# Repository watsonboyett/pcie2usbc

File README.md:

# miniPCIe to USB-C Adaptoid

A PCIe to USB-C adapter board -- plugs into a PCIe 1x card slot to breakout the data and clock lanes to a USB-C connector. 
Includes AC coupling caps and jumper resistors to aid in debugging/hacking.
Tested up to PCIe Gen 2 at 5.0 Gbps (though threre's plenty of room for improving the signal integrity).

[*] in 2nd step updating to PCIe 3.0 Standart

### Schematic

#### 
#### 
#### 

### PCB Bottom Side

#### 

### PCB Top Side

####

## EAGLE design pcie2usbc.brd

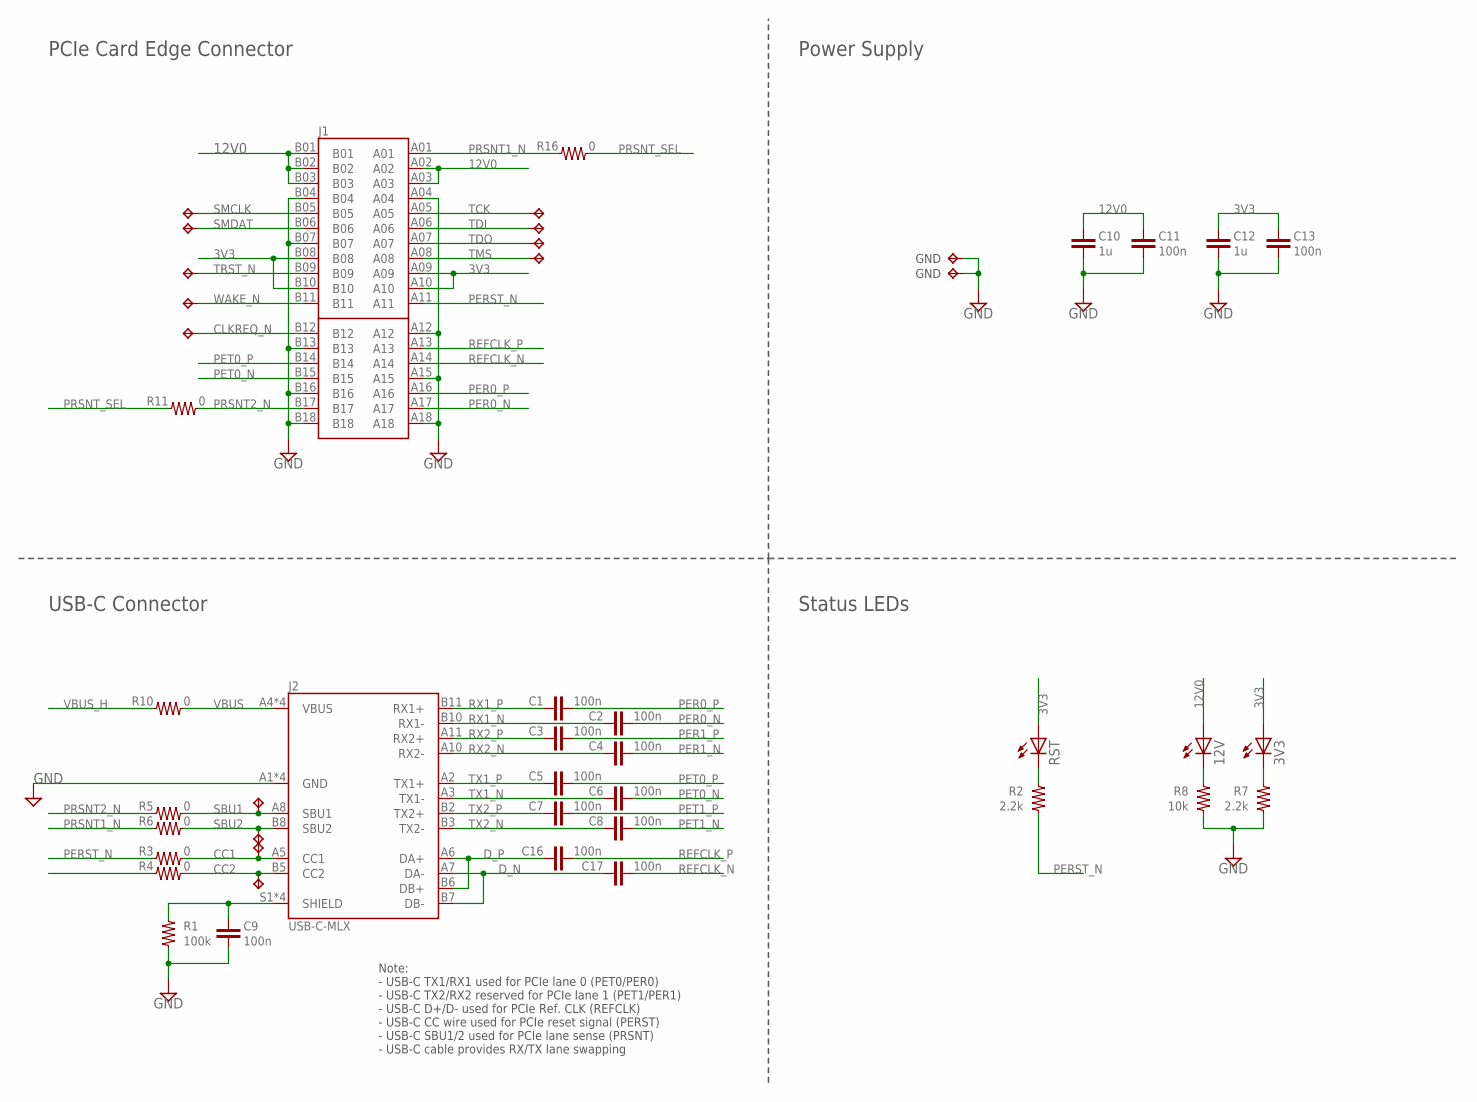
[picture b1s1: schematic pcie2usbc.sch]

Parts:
3V3, 12V: LEDSML0805; SML0805
C1, C2, C3, C4, C5, C6, C7, C8, C16, C17: 100n; C0402
C9, C11, C13: 100n; C0603K; MPN CC0603KRX7R8BB104
C10, C12: 1u; C0603K; MPN CC0603KRX7R8BB104
J1: PCIE-036-02-X-D-EMS2; SAMTEC_PCIE-036-02-X-D-EMS2
J2: USB-C-MLX; MOLEX_105450-0101
R1: 100k; R0603; MPN RC0603FR-07100KL
R2, R7: 2.2k; R0603
R3, R4, R5, R6, R10, R11, R16: 0; R0603
R8: 10k; R0603
RST: LEDSML0805; SML0805
TP1, TP2, TP3, TP4, TP5, TP6, TP7, TP8, TP9, TP11, TP12, TP16, TP21: TPB0,635; B0,635
TP10, TP13: TPTP38X20; TP38X20

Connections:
3V3: 3V3.A, C12.1, C13.1, J1.A09, J1.A10, J1.B08, J1.B10, RST.A
12V0: 12V.A, C10.1, C11.1, J1.A02, J1.A03, J1.B01, J1.B02, J1.B03
CC1: J2.A5 (CC1), R3.2, TP21.TP
CC2: J2.B5 (CC2), R4.1, TP16.TP
CLKREQ_N: J1.B12, TP9.TP
D_N: C17.1, J2.A7 (DA-), J2.B7 (DB-)
D_P: C16.1, J2.A6 (DA+), J2.B6 (DB+)
GND: C9.2, C10.2, C11.2, C12.2, C13.2, J1.A04, J1.A12, J1.A15, J1.A18, J1.B04, J1.B07, J1.B13, J1.B16, J1.B18, J2.A1 (GND), J2.A12 (GND), J2.B1 (GND), J2.B12 (GND), R1.1, R7.1, R8.1, TP10.TP, TP13.TP
unnamed: 12V.C, R8.2
unnamed: 3V3.C, R7.2
unnamed: R2.2, RST.C
PER0_N: C2.2, J1.A17
PER0_P: C1.2, J1.A16
PER1_N: C4.2
PER1_P: C3.2
PERST_N: J1.A11, R2.1, R3.1
PET0_N: C6.2, J1.B15
PET0_P: C5.2, J1.B14
PET1_N: C8.2
PET1_P: C7.2
PRSNT1_N: J1.A01, R6.1, R16.1
PRSNT2_N: J1.B17, R5.1, R11.2
PRSNT_SEL: R11.1, R16.2
REFCLK_N: C17.2, J1.A14
REFCLK_P: C16.2, J1.A13
RX1_N: C2.1, J2.B10 (RX1-)
RX1_P: C1.1, J2.B11 (RX1+)
RX2_N: C4.1, J2.A10 (RX2-)
RX2_P: C3.1, J2.A11 (RX2+)
SBU1: J2.A8 (SBU1), R5.2, TP11.TP
SBU2: J2.B8 (SBU2), R6.2, TP12.TP
SMCLK: J1.B05, TP5.TP
SMDAT: J1.B06, TP6.TP
TCK: J1.A05, TP1.TP
TDI: J1.A06, TP2.TP
TDO: J1.A07, TP3.TP
TMS: J1.A08, TP4.TP
TRST_N: J1.B09, TP7.TP
TX1_N: C6.1, J2.A3 (TX1-)
TX1_P: C5.1, J2.A2 (TX1+)
TX2_N: C8.1, J2.B3 (TX2-)
TX2_P: C7.1, J2.B2 (TX2+)
USB_SHLD1: C9.1, J2.S1 (SHIELD), J2.S2 (SHIELD), J2.S3 (SHIELD), J2.S4 (SHIELD), R1.2
VBUS: J2.A4 (VBUS), J2.A9 (VBUS), J2.B4 (VBUS), J2.B9 (VBUS), R10.2
VBUS_H: R10.1
WAKE_N: J1.B11, TP8.TP

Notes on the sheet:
PCIe Card Edge Connector
USB-C Connector
Power Supply
Note: - USB-C TX1/RX1 used for PCIe lane 0 (PET0/PER0) - USB-C TX2/RX2 reserved for PCIe lane 1 (PET1/PER1) - USB-C D+/D- used for PCIe Ref. CLK (REFCLK) - USB-C CC wire used for PCIe reset signal (PERST) - USB-C SBU1/2 used for PCIe lane sense (PRSNT) - USB-C cable provides RX/TX lane swapping
Status LEDs

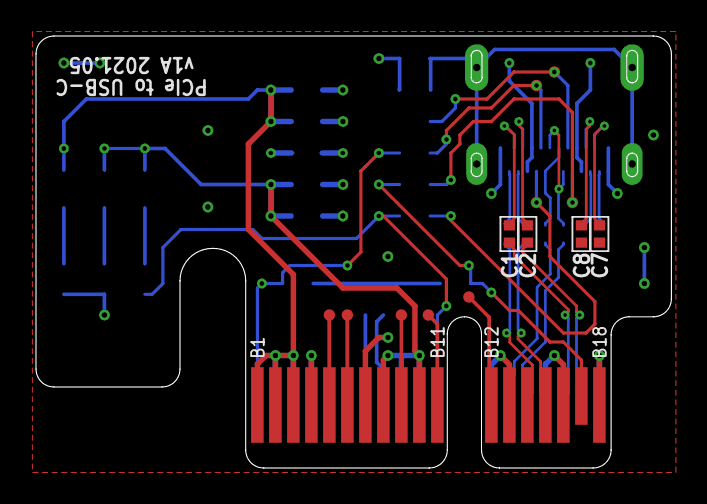
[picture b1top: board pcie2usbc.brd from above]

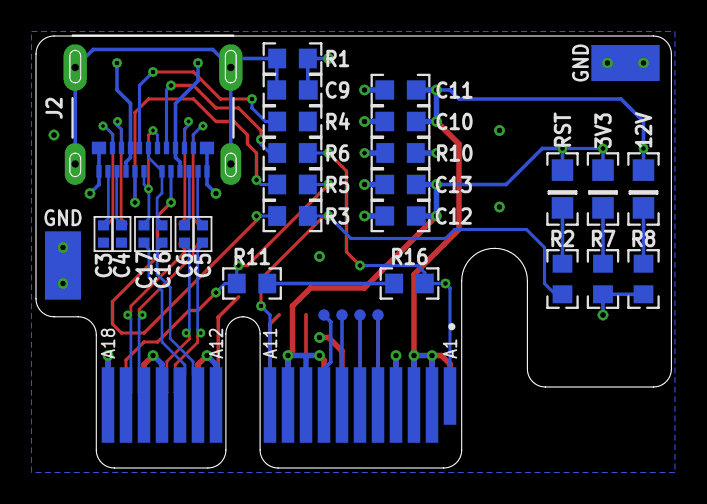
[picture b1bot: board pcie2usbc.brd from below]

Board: 4 copper layers, 35.3 x 24.0 mm, 46 parts (33 on the bottom side), 41 nets.

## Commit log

2023-08-18 KiCad 4x version -- work in progress
2023-09-12 WIP - fine tune routing
    WIP - fine tune routing
2023-09-13 Layout completed
    Layout completed
2023-09-13 final Layout
    Layout done
2023-09-15 Layout completed / Readme updar
    finalized layout
    README.me updated

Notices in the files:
pcie2usbc.sch:
LICENSE: CC-BY-SA
